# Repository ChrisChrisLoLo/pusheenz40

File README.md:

# pusheenz40
An experimental ultraportable pocket keyboard that uses low profile SMD mouse switches (EVQP0N02B) to achieve a compact form factor (8mm thick) while still being viable as a daily use keyboard (85+ wpm). Entire PCBA can be produced by JLCPCB. Uses 3D printed keycaps.

# Status
v0.0 PCBs are working! A pcb produced from the files should work.

Disclaimer is that this design has very low tolerances for its key switches. You will likely need a 3D printer such as a Bambu Lab A1/A1 mini/P1P/P1S and set the slicing layer resolution to 0.08mm. Printers like the Prusa i3/mini may also work, but have not been tested.

If you want to assemble/order your own PCBAs, come chat in the discord here! https://discord.gg/m8vwnqJEsc

# About
I hit the limit as how small I could go with choc switches. For my bunchiez40 and modkipz40, I used kailh mute switches as a smaller alternative. While a good start, these switches are both fairly tall and not super comfortable to type on directly. This board alternatively uses SMD EVQP0N02B switches from LCSC, which lowers the board height considerably, and reduces manual assembly required. This board also uses 3D printed buttons, which makes keypresses more comfortable.

More details about my research on mouse switches and experience with the pusheenz40 can be found here: https://chrischrislolo.github.io/orthoLabLogs/pusheenz40.html

Case files include 3MF files, STEP files that include the top case housing, as well as the buttons.

# Case
The case files can be found in the `case` directory. There is either the inverted rails or simple rails model to choose from. The simple rails model can be cnc'd, but has a rare tendency to have the buttons stick when pressed at a weird angle (1/1000 presses, as a rough guage of frequency). The inverted rails model has less of this issue, but cannot be cnc'd due to its sharp edges. I currently daily drive with the simple rails model.

3D printed cases can and should use the finest resolution possible on your printer, and ideally should use a higher end printer due to it's low tolerances. The models have been tested to work with the Bambu lab A1 and P1S at a layer height and detail setting of 0.08mm (extra fine). It's recommended to use a high quality and/or a newer printer.

Lubricating the case rails with something like krytox 205g0 is recommended, especially when using a CNC aluminum case. 

## PCB
You can find the PCB source files in the `pcb` folder. The BOM files can be found in this folder.

## Directory Structure
- `case`
    You can find the files you need in this folder to print out a case for the keyboard
- `drafts`
    Stores any ergogen or intermediate information used in making the case
- `pcb`
    Kicad project relating to the project. Contains the BOM, placement files, and gerbers
   
## BOM
- 1 PCBA
  - The PCB will include all electrical parts required, including switches.
- 1 Aluminum CNC upper case or 3DP upper case
- 40 3D printed buttons
- 8 3mm M1.6 screws (go for flathead for a more flush fit, though other head types should also work)
- 4-8 (ideally 8) 1-2mm bumpons (something like Sj5302 is a good place to start)

## Assembly
Flash the pcb via QMK (see below section). Bootmagic is enabled, so using the top left key to flash from here on out is doable.

Pop the 3D printed buttons/keycaps into the case, and make sure they don't stick and can freely move up and down. If they do stick (e.g. need noticable force applied to pop out), confirm that you're printing at the finest detail setting. All keys need to be flush against the case. Once the switches are in place, over lap the pcb over the case. Gently press the pcb to make sure a button isn't pressed down.

Optionally wrap the board with a rubber band to hold it in place and flip it over to validate everything. Then gently press every button to make sure if it can actuate. If a button is very sticky, reprinting or sanding may be required. If there's slight friction on the keys return, this should slowly go away as the keyboard is broken in. If there's a button that won't actuate, it's possible that the button is misaligned. Flip the board back around, remove the rubber band and pcb, and make sure the problematic key is flush against the case. Place back pcb around and test until all keys properly acutate.

Then turn the keybard around one last time so the pcb is facing upwards. Screw on the screws and test one last time.

Finally, place on the rubber bumpons

## Firmware
QMK Firmware can be found here
https://github.com/ChrisChrisLoLo/vial-qmk/tree/sporewoh/keyboards/sporewoh/pusheenz40

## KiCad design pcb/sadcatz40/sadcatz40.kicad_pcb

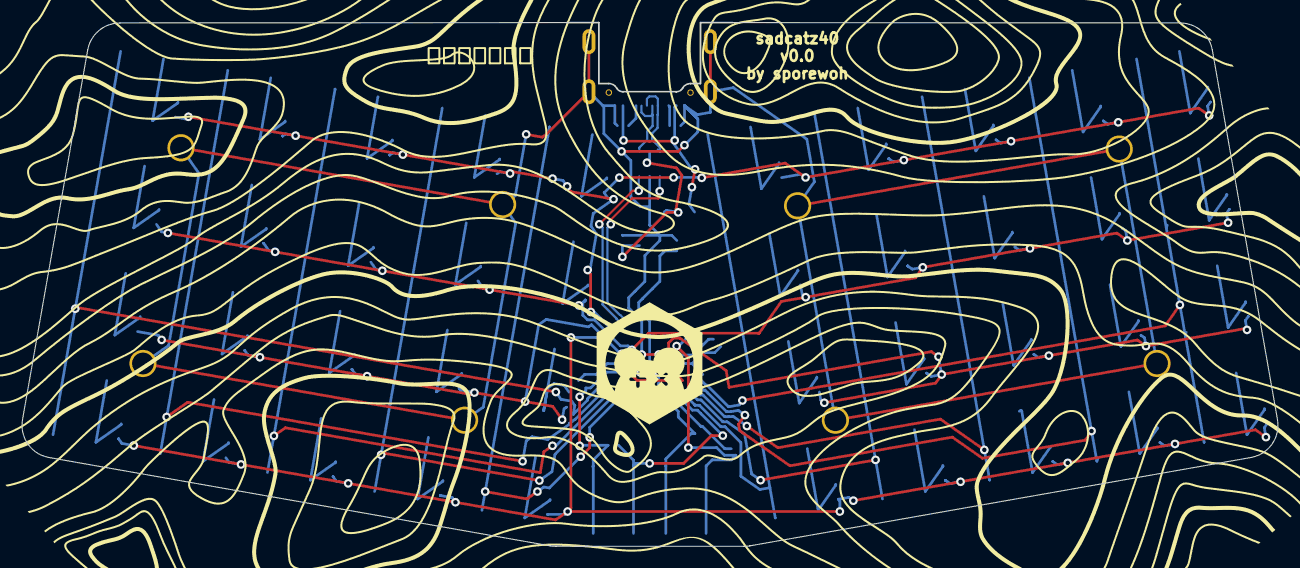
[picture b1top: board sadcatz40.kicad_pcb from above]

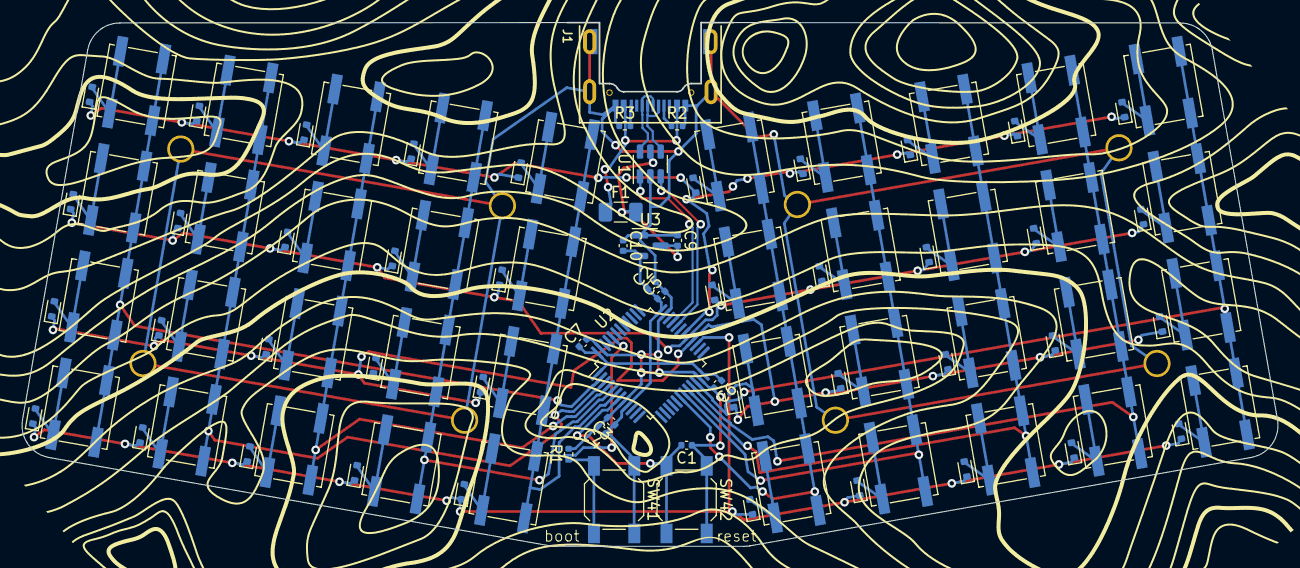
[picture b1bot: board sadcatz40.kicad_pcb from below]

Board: 2 copper layers, 115.3 x 48.1 mm, 107 parts (107 on the bottom side), 66 nets.

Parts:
C1, C4, C5, C6, C7: 100nF; C_0402_1005Metric
C2: 4.7uF; C_0402_1005Metric
C3, C9, C10: 1uF; C_0402_1005Metric
D1, D2, D3, D4, D5, D6, D7, D8, D9, D10, D11, D12, D13, D14, D15, D16, D17, D18, D19, D20, D21, D22, D23, D24, D25, D26, D27, D28, D29, D30, D31, D32, D33, D34, D35, D36, D37, D38, D39, D40: D_Small; D_SOD-523
F1: 500mA; Fuse_1206_3216Metric
H1, H2, H3, H4, H5, H6, H7, H8: MountingHole_Pad; m1.6_hole
J1: USB2_C_Receptacle; Mid_Mount-USB_C
R1: 10k; R_0402_1005Metric
R2, R3: 5.1k; R_0402_1005Metric
SW1, SW2, SW3, SW4, SW5, SW6, SW7, SW8, SW9, SW10, SW11, SW12, SW13, SW14, SW15, SW16, SW17, SW18, SW19, SW20, SW21, SW22, SW23, SW24, SW25, SW26, SW27, SW28, SW29, SW30, SW31, SW32, SW33, SW34, SW35, SW36, SW37, SW38, SW39, SW40: SW_Push; SW_SPST_EVQP0
SW41: BOOT; SW_SPST_SKQG_WithoutStem
SW42: RST; SW_SPST_SKQG_WithoutStem
U1: USBLC6-2SC6; SOT-23-6
U2: STM32F072C8Tx; LQFP-48_7x7mm_P0.5mm
U3: XC6206PxxxMR-Regulator_Linear; SOT-23

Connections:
+3V3: C2.1, C3.1, C4.1, C5.1, C6.1, C7.1, C10.2, SW41.1, U2.1 (VBAT), U2.9 (VDDA), U2.24 (VDD), U2.36 (VDDIO2), U2.48 (VDD), U3.2 (VO)
+5V: C9.2, F1.2, U1.5 (VBUS), U3.3 (VI)
BOOT0: R1.1, SW41.2, U2.44 (BOOT0)
COL1: SW1.2, SW11.2, SW21.2, SW31.2, U2.22 (PB11)
COL2: SW2.2, SW12.2, SW22.2, SW32.2, U2.2 (PC13)
COL3: SW3.2, SW13.2, SW23.2, SW33.2, U2.21 (PB10)
COL4: SW4.2, SW14.2, SW24.2, SW34.2, U2.3 (PC14)
COL5: SW5.2, SW15.2, SW25.2, SW35.2, U2.20 (PB2)
COL6: SW6.2, SW16.2, SW26.2, SW36.2, U2.4 (PC15)
COL7: SW7.2, SW17.2, SW27.2, SW37.2, U2.19 (PB1)
COL8: SW8.2, SW18.2, SW28.2, SW38.2, U2.5 (PF0)
COL9: SW9.2, SW19.2, SW29.2, SW39.2, U2.18 (PB0)
COL10: SW10.2, SW20.2, SW30.2, SW40.2, U2.6 (PF1)
D_N: U1.3 (I/O2), U2.32 (PA11)
D_P: U1.1 (I/O1), U2.33 (PA12)
D_USB_+: J1.A6 (D+), J1.B6 (D+), U1.6 (I/O1)
D_USB_-: J1.A7 (D-), J1.B7 (D-), U1.4 (I/O2)
GND: C1.1, C2.2, C3.2, C4.2, C5.2, C6.2, C7.2, C9.1, C10.1, H1.1, H2.1, H3.1, H4.1, H5.1, H6.1, H7.1, H8.1, J1.A1B12 (GND), J1.B1A12 (GND), J1.S1 (Shield), R1.2, R2.2, R3.1, SW42.1, U1.2 (GND), U2.8 (VSSA), U2.23 (VSS), U2.35 (VSS), U2.47 (VSS), U3.1 (GND)
NRST: C1.2, SW42.2, U2.7 (NRST)
unnamed: D1.2 (A), SW1.1
unnamed: D2.2 (A), SW2.1
unnamed: D3.2 (A), SW3.1
unnamed: D4.2 (A), SW4.1
unnamed: D5.2 (A), SW5.1
unnamed: D6.2 (A), SW6.1
unnamed: D7.2 (A), SW7.1
unnamed: D8.2 (A), SW8.1
unnamed: D9.2 (A), SW9.1
unnamed: D10.2 (A), SW10.1
unnamed: D11.2 (A), SW11.1
unnamed: D12.2 (A), SW12.1
unnamed: D13.2 (A), SW13.1
unnamed: D14.2 (A), SW14.1
unnamed: D15.2 (A), SW15.1
unnamed: D16.2 (A), SW16.1
unnamed: D17.2 (A), SW17.1
unnamed: D18.2 (A), SW18.1
unnamed: D19.2 (A), SW19.1
unnamed: D20.2 (A), SW20.1
unnamed: D21.2 (A), SW21.1
unnamed: D22.2 (A), SW22.1
unnamed: D23.2 (A), SW23.1
unnamed: D24.2 (A), SW24.1
unnamed: D25.2 (A), SW25.1
unnamed: D26.2 (A), SW26.1
unnamed: D27.2 (A), SW27.1
unnamed: D28.2 (A), SW28.1
unnamed: D29.2 (A), SW29.1
unnamed: D30.2 (A), SW30.1
unnamed: D31.2 (A), SW31.1
unnamed: D32.2 (A), SW32.1
unnamed: D33.2 (A), SW33.1
unnamed: D34.2 (A), SW34.1
unnamed: D35.2 (A), SW35.1
unnamed: D36.2 (A), SW36.1
unnamed: D37.2 (A), SW37.1
unnamed: D38.2 (A), SW38.1
unnamed: D39.2 (A), SW39.1
unnamed: D40.2 (A), SW40.1
unnamed: J1.A5 (CC1), R2.1
unnamed: J1.B5 (CC2), R3.2
ROW1: D1.1 (K), D2.1 (K), D3.1 (K), D4.1 (K), D5.1 (K), D6.1 (K), D7.1 (K), D8.1 (K), D9.1 (K), D10.1 (K), U2.30 (PA9)
ROW2: D11.1 (K), D12.1 (K), D13.1 (K), D14.1 (K), D15.1 (K), D16.1 (K), D17.1 (K), D18.1 (K), D19.1 (K), D20.1 (K), U2.29 (PA8)
ROW3: D21.1 (K), D22.1 (K), D23.1 (K), D24.1 (K), D25.1 (K), D26.1 (K), D27.1 (K), D28.1 (K), D29.1 (K), D30.1 (K), U2.28 (PB15)
ROW4: D31.1 (K), D32.1 (K), D33.1 (K), D34.1 (K), D35.1 (K), D36.1 (K), D37.1 (K), D38.1 (K), D39.1 (K), D40.1 (K), U2.27 (PB14)
VBUS: F1.1, J1.A4B9 (VBUS), J1.B4A9 (VBUS)

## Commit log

2023-12-20 init commit
2023-12-22 add outlines
2023-12-23 tighten key tolerance
2023-12-25 tighten tolerances
2024-01-29 update pcb
2024-01-29 add cases and readme
2024-02-02 add bom and placement
2024-02-03 add fusion360 source files B)
